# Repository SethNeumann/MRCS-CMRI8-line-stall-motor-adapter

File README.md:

# REPO NAME: MRCS-CMRI8-line-stall-motor-adpater

## License: Creative Commons Attribution-NonCommercial-ShareAlike

DThis is part of our 8 line (byte-wide) adapters for classic CMRI boards such as the DIN/DOUT [24/32] and SMINI.  By mixing and matching you can convert the male 
Molex (0.156) pins to screw terminal breaks in 0.100", 3.5mm, 0.156" or RJ45.  This board supports the simple "shunt" style stall motor control suggested by 
Dr. Chubb in his CMRI User's manual  Version 3.0 on pages 3-14  and 3-15.

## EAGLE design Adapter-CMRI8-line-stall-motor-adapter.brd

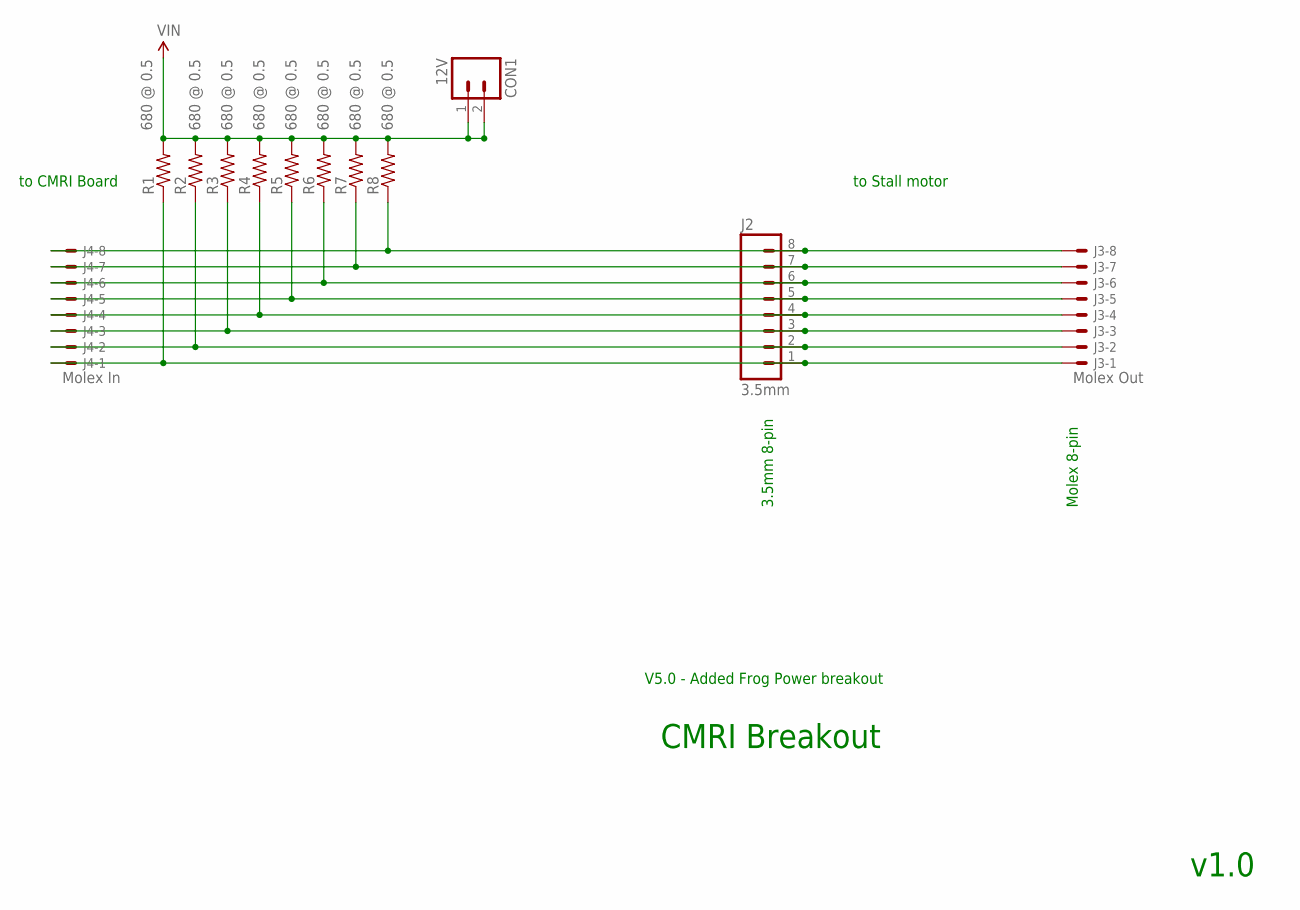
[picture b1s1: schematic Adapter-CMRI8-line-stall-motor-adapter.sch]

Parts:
CON1: 12V; SCREWTERMINAL-3.5MM-2_LOCK
J2: 3.5mm; SCREWTERMINAL-3.5MM-8
J3: Molex Out; KK-156-8-F
J4: Molex In; KK-156-8-F
R1, R2, R3, R4, R5, R6, R7, R8: 680 @ 0.5; AXIAL-0.5

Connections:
L2: J2.2, J3.2, J4.2, R2.P$1 (1)
L3: J2.3, J3.3, J4.3, R3.P$1 (1)
L5: J2.5, J3.5, J4.5, R5.P$1 (1)
L6: J2.6, J3.6, J4.6, R6.P$1 (1)
L7: J2.7, J3.7, J4.7, R7.P$1 (1)
L8: J2.8, J3.8, J4.8, R8.P$1 (1)
unnamed: J2.1, J3.1, J4.1, R1.P$1 (1)
unnamed: J2.4, J3.4, J4.4, R4.P$1 (1)
VIN: CON1.1 (A), CON1.2 (B), R1.P$2 (2), R2.P$2 (2), R3.P$2 (2), R4.P$2 (2), R5.P$2 (2), R6.P$2 (2), R7.P$2 (2), R8.P$2 (2)

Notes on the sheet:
Molex 8-pin
3.5mm 8-pin
CMRI Breakout
v1.0
V5.0 - Added Frog Power breakout
to CMRI Board
to Stall motor

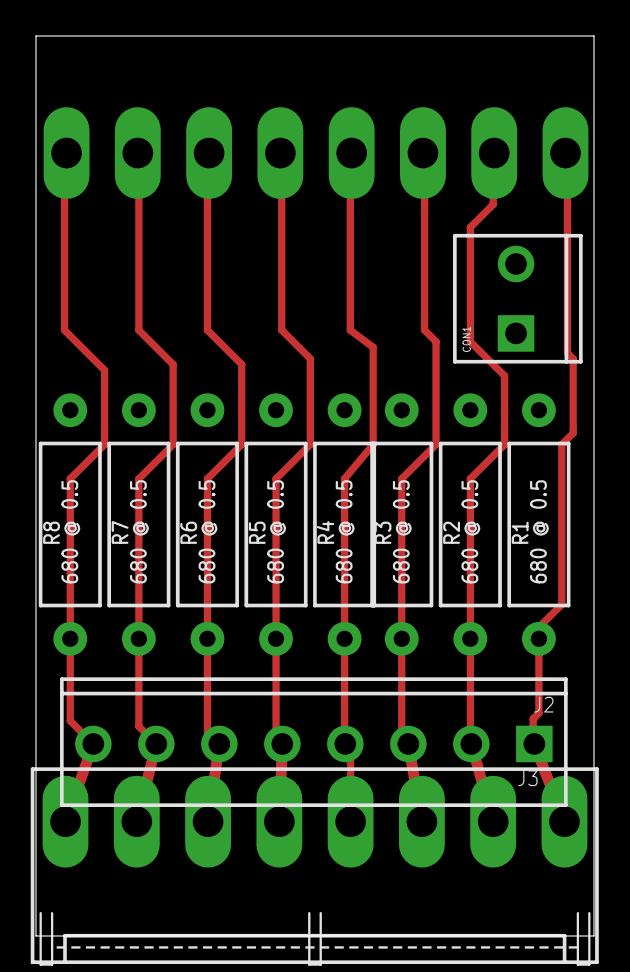
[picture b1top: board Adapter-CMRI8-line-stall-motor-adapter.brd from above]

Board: 2 copper layers, 31.0 x 50.0 mm, 14 parts (1 on the bottom side), 9 nets.

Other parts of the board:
U$1: CA-PROP65WARNING
U$2: MRCSLOGOBTM

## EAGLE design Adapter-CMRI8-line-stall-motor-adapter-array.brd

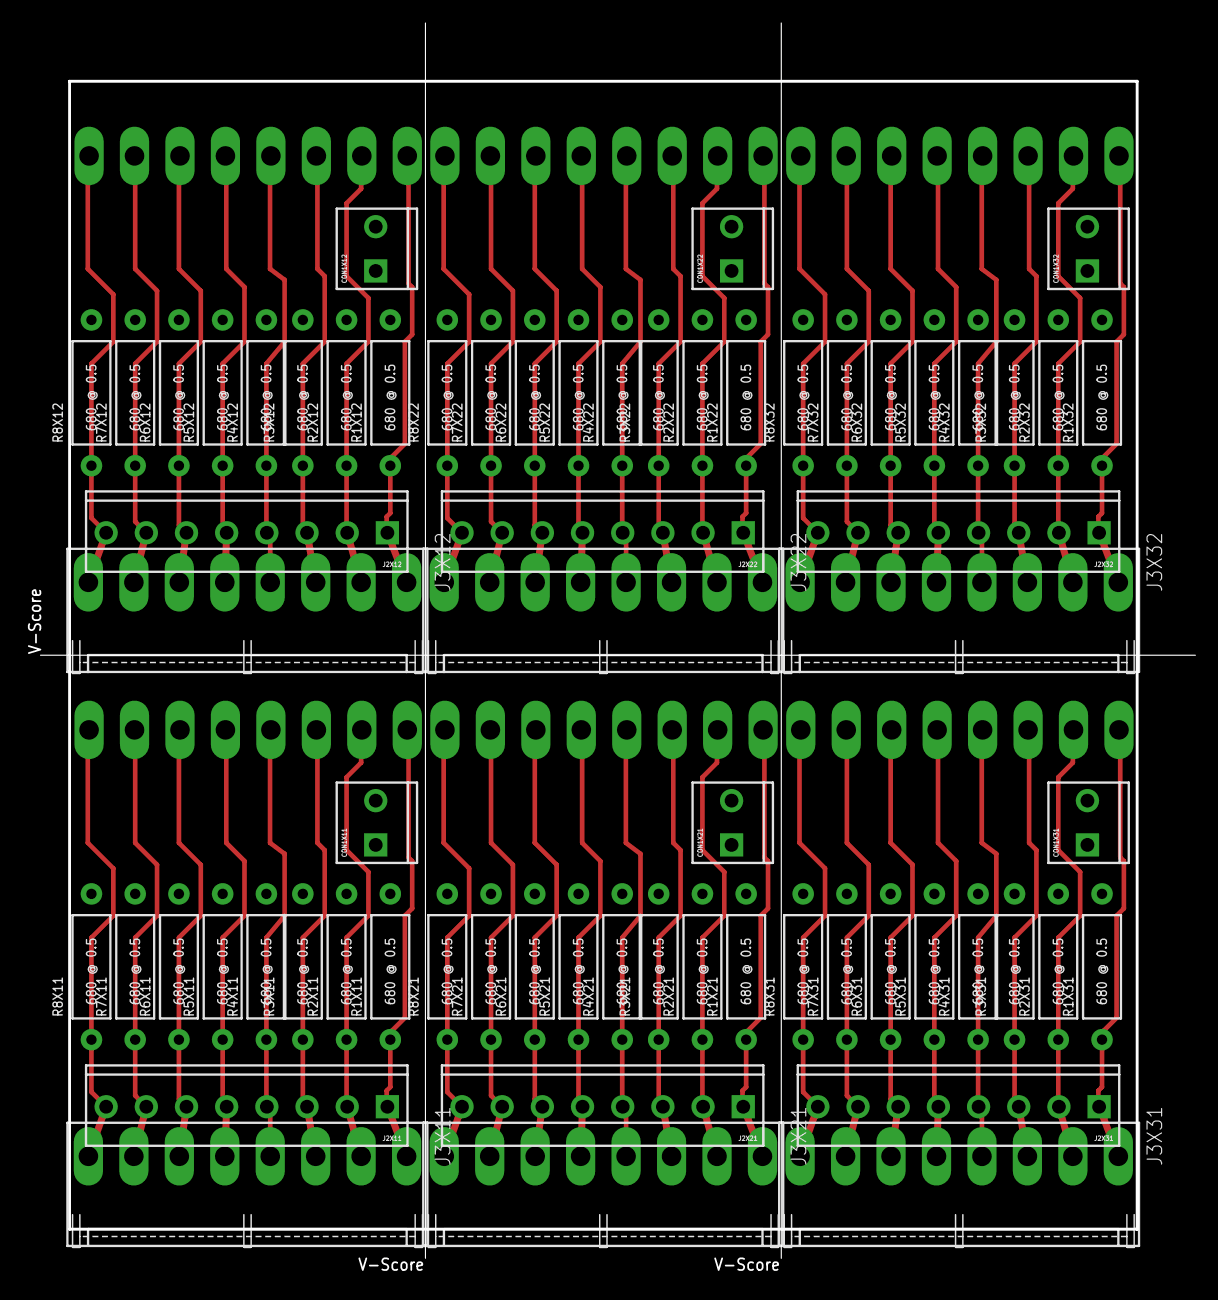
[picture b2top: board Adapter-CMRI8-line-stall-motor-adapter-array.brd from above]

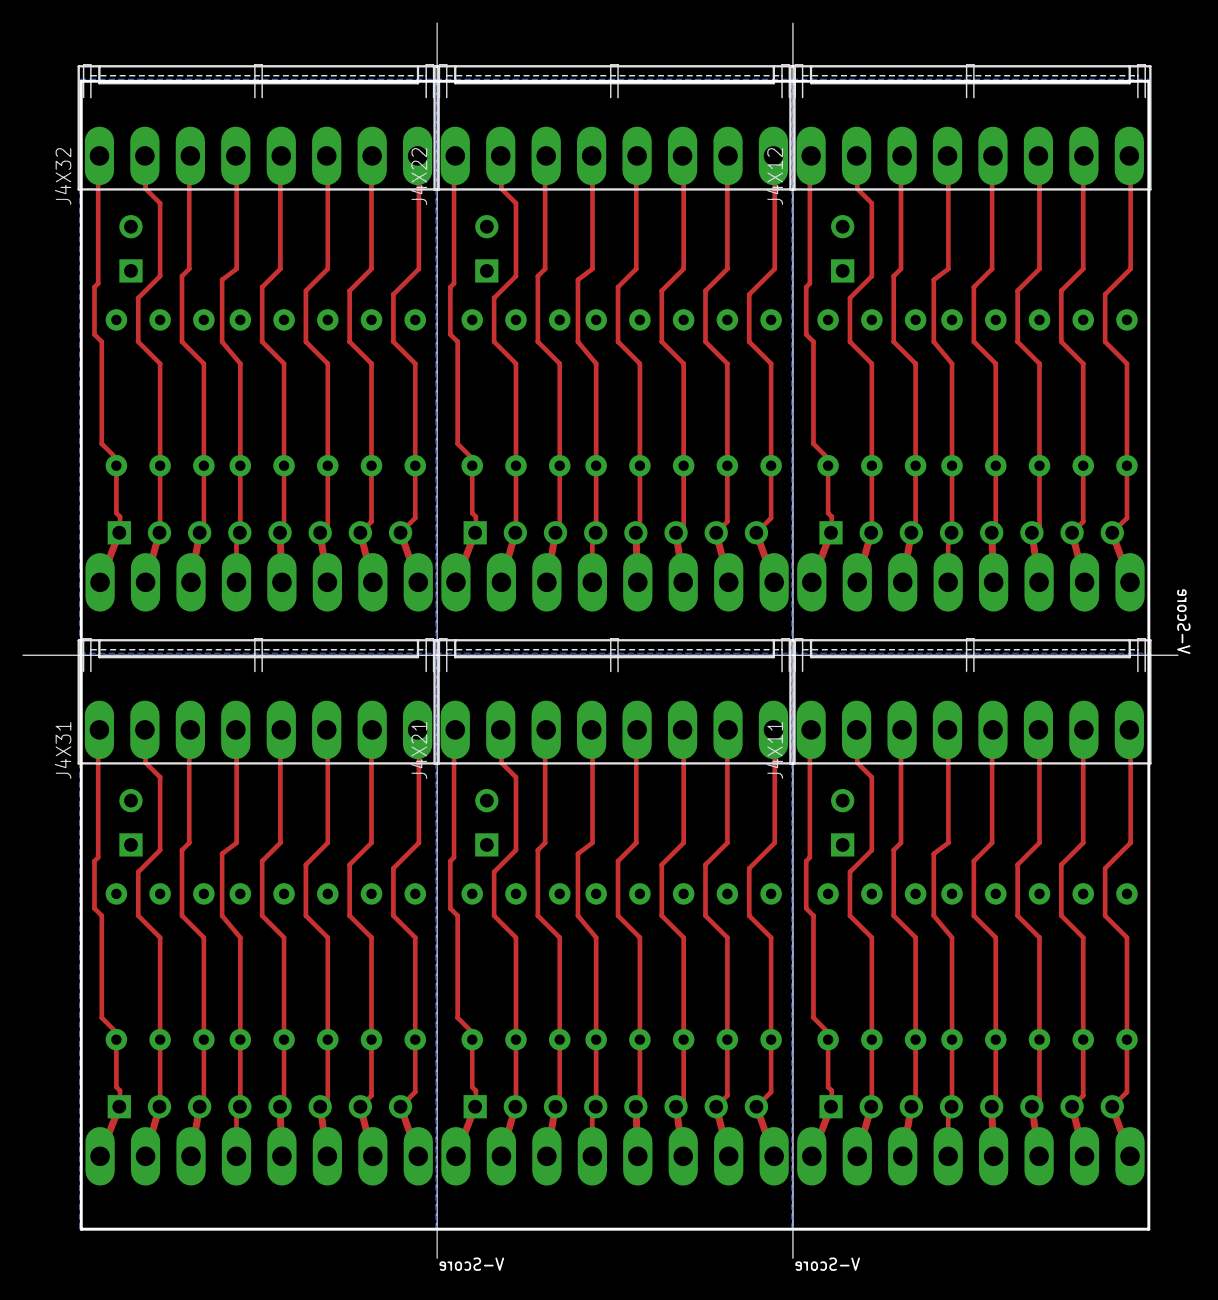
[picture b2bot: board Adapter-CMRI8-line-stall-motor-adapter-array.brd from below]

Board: 2 copper layers, 100.6 x 107.6 mm, 84 parts (6 on the bottom side), 54 nets.

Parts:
CON1X11, CON1X12, CON1X21, CON1X22, CON1X31, CON1X32: 12V; SCREWTERMINAL-3.5MM-2_LOCK
J2X11, J2X12, J2X21, J2X22, J2X31, J2X32: 3.5mm; SCREWTERMINAL-3.5MM-8
J3X11, J3X12, J3X21, J3X22, J3X31, J3X32: Molex Out; KK-156-8-F
J4X11, J4X12, J4X21, J4X22, J4X31, J4X32: Molex In; KK-156-8-F
R1X11, R1X12, R1X21, R1X22, R1X31, R1X32, R2X11, R2X12, R2X21, R2X22, R2X31, R2X32, R3X11, R3X12, R3X21, R3X22, R3X31, R3X32, R4X11, R4X12, R4X21, R4X22, R4X31, R4X32, R5X11, R5X12, R5X21, R5X22, R5X31, R5X32, R6X11, R6X12, R6X21, R6X22, R6X31, R6X32, R7X11, R7X12, R7X21, R7X22, R7X31, R7X32, R8X11, R8X12, R8X21, R8X22, R8X31, R8X32: 680 @ 0.5; AXIAL-0.5
U$1X11, U$1X12, U$1X21, U$1X22, U$1X31, U$1X32: CA-PROP65WARNING
U$2X11, U$2X12, U$2X21, U$2X22, U$2X31, U$2X32: MRCSLOGOBTM

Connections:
L2X11: J2X11.2, J3X11.2, J4X11.2, R2X11.P$1
L2X12: J2X12.2, J3X12.2, J4X12.2, R2X12.P$1
L2X21: J2X21.2, J3X21.2, J4X21.2, R2X21.P$1
L2X22: J2X22.2, J3X22.2, J4X22.2, R2X22.P$1
L2X31: J2X31.2, J3X31.2, J4X31.2, R2X31.P$1
L2X32: J2X32.2, J3X32.2, J4X32.2, R2X32.P$1
L3X11: J2X11.3, J3X11.3, J4X11.3, R3X11.P$1
L3X12: J2X12.3, J3X12.3, J4X12.3, R3X12.P$1
L3X21: J2X21.3, J3X21.3, J4X21.3, R3X21.P$1
L3X22: J2X22.3, J3X22.3, J4X22.3, R3X22.P$1
L3X31: J2X31.3, J3X31.3, J4X31.3, R3X31.P$1
L3X32: J2X32.3, J3X32.3, J4X32.3, R3X32.P$1
L5X11: J2X11.5, J3X11.5, J4X11.5, R5X11.P$1
L5X12: J2X12.5, J3X12.5, J4X12.5, R5X12.P$1
L5X21: J2X21.5, J3X21.5, J4X21.5, R5X21.P$1
L5X22: J2X22.5, J3X22.5, J4X22.5, R5X22.P$1
L5X31: J2X31.5, J3X31.5, J4X31.5, R5X31.P$1
L5X32: J2X32.5, J3X32.5, J4X32.5, R5X32.P$1
L6X11: J2X11.6, J3X11.6, J4X11.6, R6X11.P$1
L6X12: J2X12.6, J3X12.6, J4X12.6, R6X12.P$1
L6X21: J2X21.6, J3X21.6, J4X21.6, R6X21.P$1
L6X22: J2X22.6, J3X22.6, J4X22.6, R6X22.P$1
L6X31: J2X31.6, J3X31.6, J4X31.6, R6X31.P$1
L6X32: J2X32.6, J3X32.6, J4X32.6, R6X32.P$1
L7X11: J2X11.7, J3X11.7, J4X11.7, R7X11.P$1
L7X12: J2X12.7, J3X12.7, J4X12.7, R7X12.P$1
L7X21: J2X21.7, J3X21.7, J4X21.7, R7X21.P$1
L7X22: J2X22.7, J3X22.7, J4X22.7, R7X22.P$1
L7X31: J2X31.7, J3X31.7, J4X31.7, R7X31.P$1
L7X32: J2X32.7, J3X32.7, J4X32.7, R7X32.P$1
L8X11: J2X11.8, J3X11.8, J4X11.8, R8X11.P$1
L8X12: J2X12.8, J3X12.8, J4X12.8, R8X12.P$1
L8X21: J2X21.8, J3X21.8, J4X21.8, R8X21.P$1
L8X22: J2X22.8, J3X22.8, J4X22.8, R8X22.P$1
L8X31: J2X31.8, J3X31.8, J4X31.8, R8X31.P$1
L8X32: J2X32.8, J3X32.8, J4X32.8, R8X32.P$1
unnamed: J2X11.1, J3X11.1, J4X11.1, R1X11.P$1
unnamed: J2X12.1, J3X12.1, J4X12.1, R1X12.P$1
unnamed: J2X21.1, J3X21.1, J4X21.1, R1X21.P$1
unnamed: J2X22.1, J3X22.1, J4X22.1, R1X22.P$1
unnamed: J2X31.1, J3X31.1, J4X31.1, R1X31.P$1
unnamed: J2X32.1, J3X32.1, J4X32.1, R1X32.P$1
unnamed: J2X11.4, J3X11.4, J4X11.4, R4X11.P$1
unnamed: J2X12.4, J3X12.4, J4X12.4, R4X12.P$1
unnamed: J2X21.4, J3X21.4, J4X21.4, R4X21.P$1
unnamed: J2X22.4, J3X22.4, J4X22.4, R4X22.P$1
unnamed: J2X31.4, J3X31.4, J4X31.4, R4X31.P$1
unnamed: J2X32.4, J3X32.4, J4X32.4, R4X32.P$1
VINX11: CON1X11.1, CON1X11.2, R1X11.P$2, R2X11.P$2, R3X11.P$2, R4X11.P$2, R5X11.P$2, R6X11.P$2, R7X11.P$2, R8X11.P$2
VINX12: CON1X12.1, CON1X12.2, R1X12.P$2, R2X12.P$2, R3X12.P$2, R4X12.P$2, R5X12.P$2, R6X12.P$2, R7X12.P$2, R8X12.P$2
VINX21: CON1X21.1, CON1X21.2, R1X21.P$2, R2X21.P$2, R3X21.P$2, R4X21.P$2, R5X21.P$2, R6X21.P$2, R7X21.P$2, R8X21.P$2
VINX22: CON1X22.1, CON1X22.2, R1X22.P$2, R2X22.P$2, R3X22.P$2, R4X22.P$2, R5X22.P$2, R6X22.P$2, R7X22.P$2, R8X22.P$2
VINX31: CON1X31.1, CON1X31.2, R1X31.P$2, R2X31.P$2, R3X31.P$2, R4X31.P$2, R5X31.P$2, R6X31.P$2, R7X31.P$2, R8X31.P$2
VINX32: CON1X32.1, CON1X32.2, R1X32.P$2, R2X32.P$2, R3X32.P$2, R4X32.P$2, R5X32.P$2, R6X32.P$2, R7X32.P$2, R8X32.P$2

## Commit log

2021-12-04 initial committ
    started with CMRI 8 line 3.5mm adapter for form factor and Molex end
2021-12-04 initial commit
    initial commit
2021-12-04 initial commit
    initial layout
2021-12-04 added the CMRI-35mm board as a start
    modifying the CMRI-3.5 mm board
2021-12-05 clean up of initial fab order
    Misc changes to clean up clearances and documentation for initial build (20211204)
2021-12-21 push after prototype singlets
    Everything works, will panelize in next board order
2022-07-05 panelized version
    panelized files and removed random gerbs

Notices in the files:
parts and their libraries:
SparkFun-Resistors: Licensing: CC v3.0 Share-Alike You are welcome to use this library for commercial purposes.
